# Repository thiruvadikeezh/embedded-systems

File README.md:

🚀 Embedded Systems Adventure Hub
Welcome to my Embedded Systems repository—a vibrant showcase of my thrilling journey into the heart of hardware and software! 🌟 Here, I explore the art & science of embedded systems, crafting innovative projects and sharing my passion for microcontrollers, sensors, and real-time tech.

🌟 About My Journey
I'm on a mission to conquer the world of embedded systems! From blinking LEDs on an Arduino to building IoT marvels with Raspberry Pi and STM32, this repo is my playground for mastering low-level programming and hardware wizardry. Expect a mix of creativity, problem-solving, and a dash of geeky fun as I dive into the nitty-gritty of embedded tech! 💻🔧

🛠 What's Inside

🔥 Exciting Projects: From smart IoT gadgets to sensor-driven systems and real-time applications, explore my hands-on creations.
💾 Code Goodies: Clean, reusable C/C++ snippets for microcontrollers, including drivers, firmware, and more.
📚 Tutorials & Insights: My personal cheat sheets on interrupts, timers, and protocols like I2C, SPI, and UART—perfect for beginners and pros alike.
🔗 Resource Treasure Trove: Curated links to tools, datasheets, and must-have references for embedded enthusiasts.

🚀 Get Started

Clone the Repo: git clone https://github.com/fatmanweb3/embedded-systems.git
Dive into Projects: Browse folders for specific platforms (Arduino, STM32, ESP32) or project types.
Set Up Your Toolkit: Grab Arduino IDE, PlatformIO, or STM32CubeIDE to jump in.
Join the Fun: Got ideas? Open an issue, suggest features, or collaborate on something epic!

🌈 What's Next?
I'm always tinkering and learning! Expect new projects, deep dives into real-time operating systems (RTOS), low-power optimizations, and advanced protocols. Follow along as I push the boundaries of what's possible in embedded systems! 🚀

🤝 Connect & Contribute
Love embedded systems? Let's geek out together! Open a pull request, share your thoughts, or just say hi. Together, we can build mind-blowing tech that powers the future. 💡
Happy hacking, and let's make some hardware magic! ✨

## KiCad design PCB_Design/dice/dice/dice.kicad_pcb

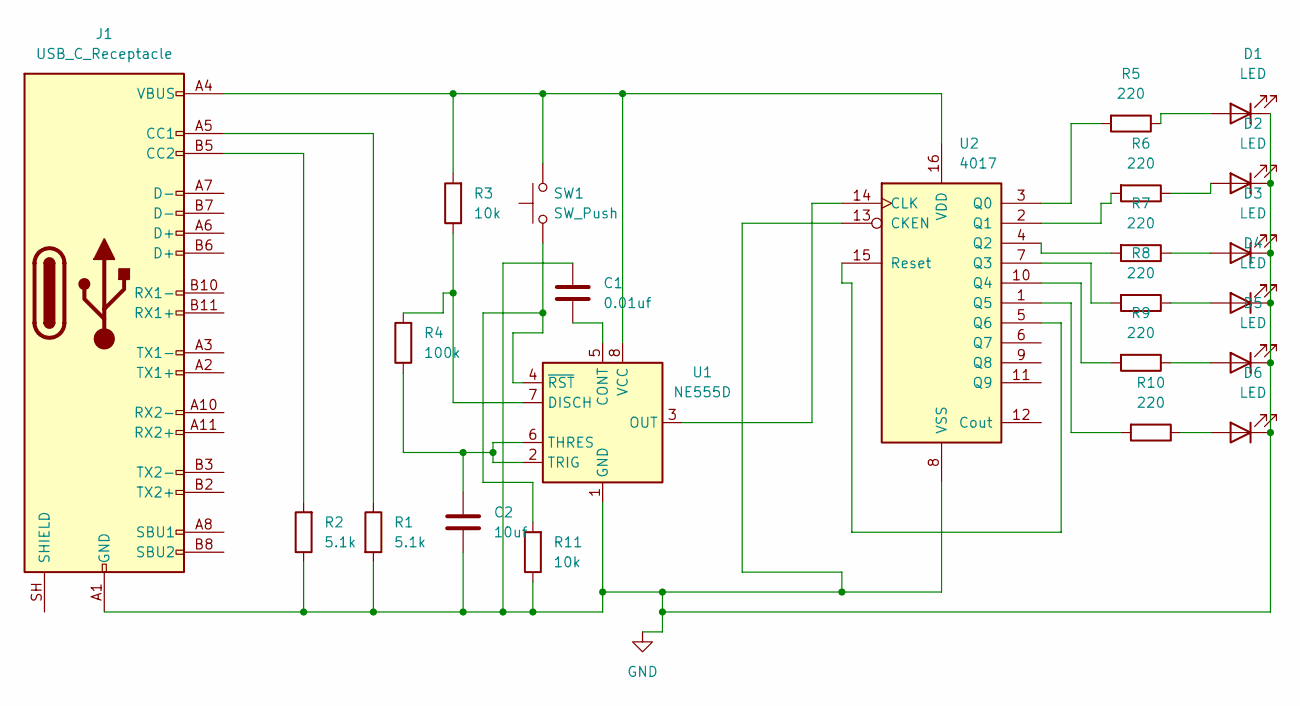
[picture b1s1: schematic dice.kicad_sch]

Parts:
C1: 0.01uf; C_0805_2012Metric
C2: 10uf; C_0805_2012Metric
D1, D2, D3, D4, D5, D6: LED; LED_0805_2012Metric
J1: USB_C_Receptacle; USB_C_Receptacle_HRO_TYPE-C-31-M-12
R1, R2: 5.1k; R_0805_2012Metric
R3, R11: 10k; R_0805_2012Metric
R4: 100k; R_0805_2012Metric
R5, R6, R7, R8, R9, R10: 220; R_0805_2012Metric
SW1: SW_Push; SW_Push_1P1T-MP_NO_Horizontal_Alps_SKRTLAE010
U1: NE555D; SOIC-8_3.9x4.9mm_P1.27mm
U2: 4017; SOIC-16_3.9x9.9mm_P1.27mm

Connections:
GND: C1.1, C2.2, D1.1 (K), D2.1 (K), D3.1 (K), D4.1 (K), D5.1 (K), D6.1 (K), J1.A1 (GND), J1.A12 (GND), J1.B1 (GND), J1.B12 (GND), R1.2, R2.1, R11.1, U1.1 (GND), U2.8 (VSS), U2.13 (CKEN)
unnamed: D1.2 (A), R5.1
unnamed: D2.2 (A), R6.1
unnamed: D3.2 (A), R7.1
unnamed: D4.2 (A), R8.1
unnamed: D5.2 (A), R9.1
unnamed: D6.2 (A), R10.1
unnamed: J1.A5 (CC1), R1.1
unnamed: J1.B5 (CC2), R2.2
unnamed: C1.2, U1.5 (CONT)
unnamed: R3.1, R4.2, U1.7 (DISCH)
unnamed: U1.3 (OUT), U2.14 (CLK)
unnamed: C2.1, R4.1, U1.2 (TRIG), U1.6 (THRES)
unnamed: J1.A4 (VBUS), J1.A9 (VBUS), J1.B4 (VBUS), J1.B9 (VBUS), R3.2, SW1.2, U1.8 (VCC), U2.16 (VDD)
unnamed: R11.2, SW1.1, U1.4 (~RST)
unnamed: R5.2, U2.3 (Q0)
unnamed: R6.2, U2.2 (Q1)
unnamed: R7.2, U2.4 (Q2)
unnamed: R8.2, U2.7 (Q3)
unnamed: R9.2, U2.10 (Q4)
unnamed: R10.2, U2.1 (Q5)
unnamed: U2.5 (Q6), U2.15 (Reset)

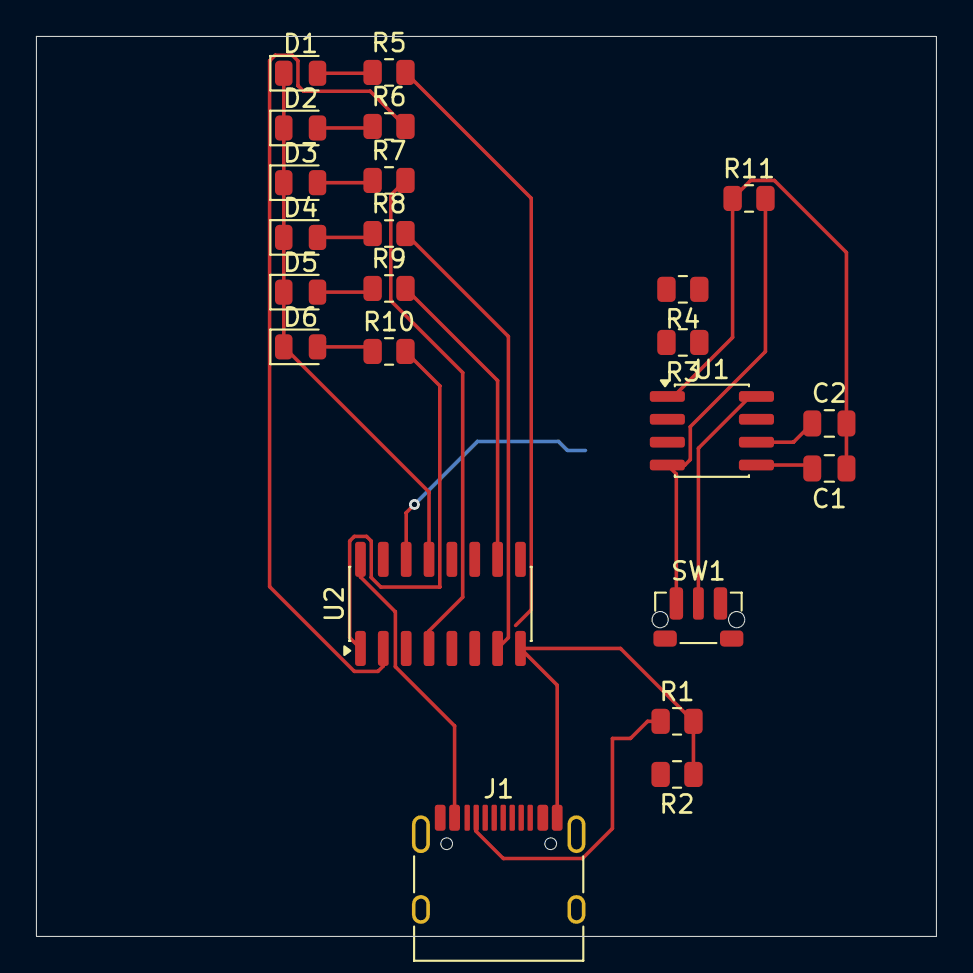
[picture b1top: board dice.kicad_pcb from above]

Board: 2 copper layers, 50.0 x 50.0 mm, 23 parts (0 on the bottom side), 22 nets.

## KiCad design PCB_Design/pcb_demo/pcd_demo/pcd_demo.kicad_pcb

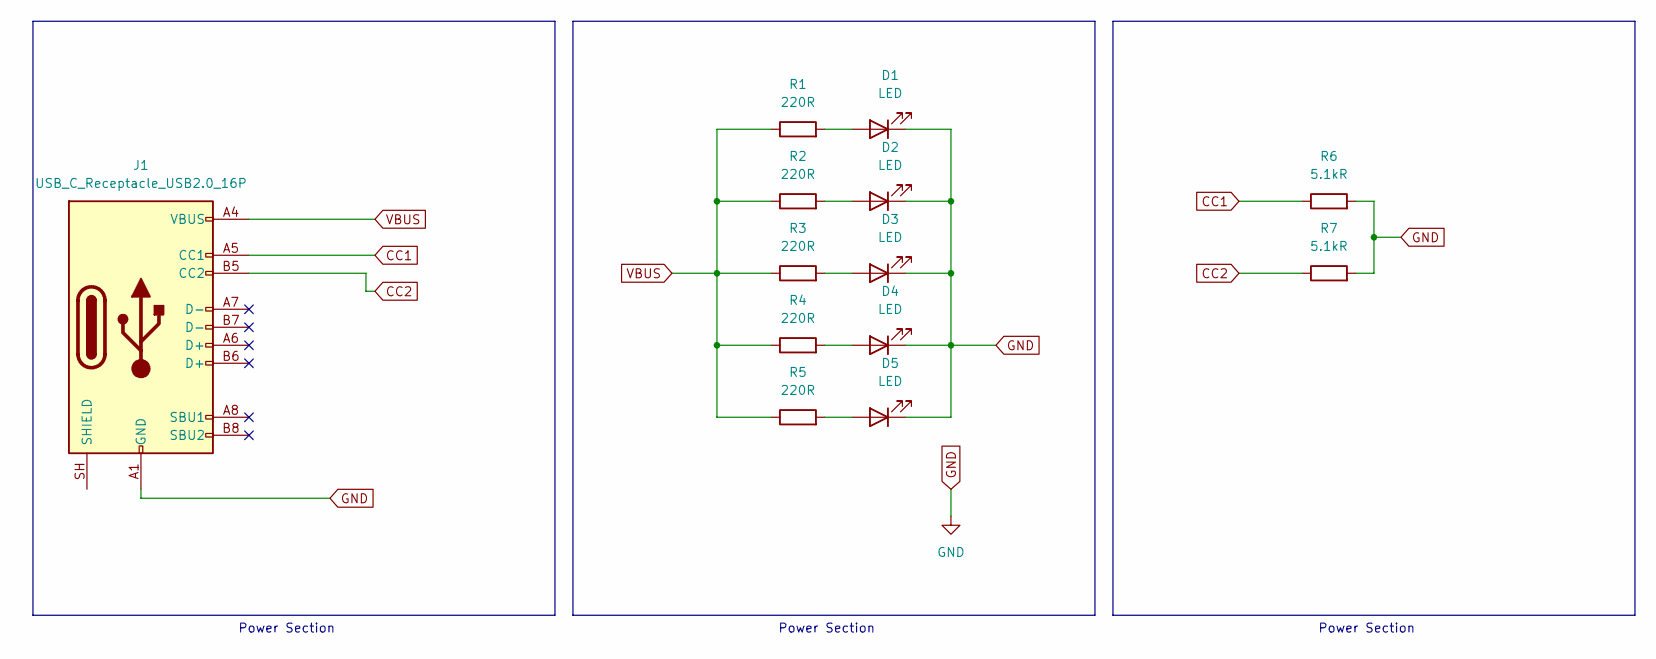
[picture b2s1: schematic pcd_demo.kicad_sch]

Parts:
D1, D2, D3, D4, D5: LED; LED_0805_2012Metric
J1: USB_C_Receptacle_USB2.0_16P
R1, R2, R3, R4, R5: 220R; R_0805_2012Metric
R6, R7: 5.1kR; R_0805_2012Metric

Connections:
CC1: J1.A5 (CC1), R6.1; also elsewhere on the board
CC2: J1.B5 (CC2), R7.1; also elsewhere on the board
GND: D1.1 (K), D2.1 (K), D3.1 (K), D4.1 (K), D5.1 (K), J1.A1 (GND), J1.A12 (GND), J1.B1 (GND), J1.B12 (GND), R6.2, R7.2; also elsewhere on the board
unnamed: D1.2 (A), R1.2
unnamed: D2.2 (A), R2.2
unnamed: D3.2 (A), R3.2
unnamed: D4.2 (A), R4.2
unnamed: D5.2 (A), R5.2
VBUS: J1.A4 (VBUS), J1.A9 (VBUS), J1.B4 (VBUS), J1.B9 (VBUS), R1.1, R2.1, R3.1, R4.1, R5.1; also elsewhere on the board

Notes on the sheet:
Power Section

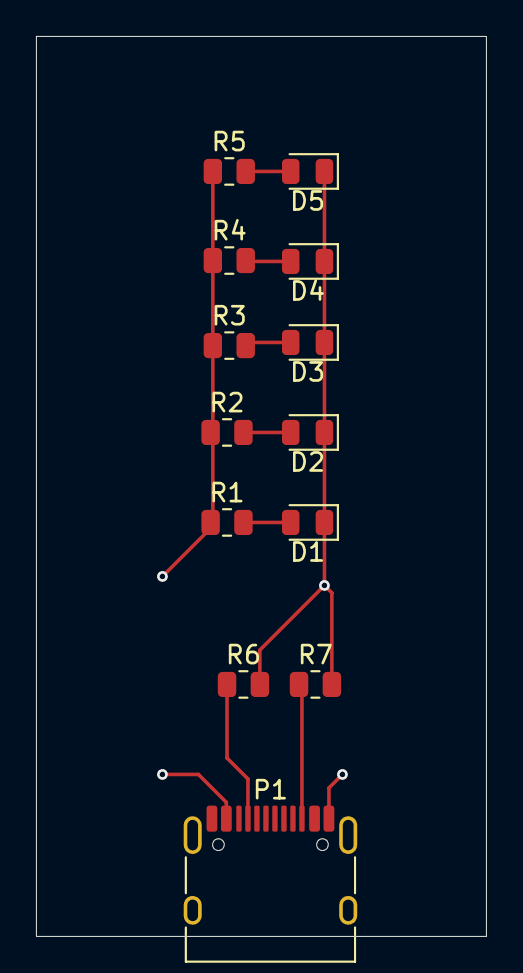
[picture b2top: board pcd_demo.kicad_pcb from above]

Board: 4 copper layers, 25.0 x 50.0 mm, 13 parts (0 on the bottom side), 9 nets.

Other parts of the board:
P1: USB_C_Plug; USB_C_Receptacle_HRO_TYPE-C-31-M-12

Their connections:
CC1: P1.A5 (CC); also elsewhere on the board
CC2: P1.B5 (VCONN); also elsewhere on the board
GND: P1.A1 (GND), P1.A12 (GND), P1.B1 (GND), P1.B12 (GND); also elsewhere on the board
VBUS: P1.A4 (VBUS), P1.A9 (VBUS), P1.B4 (VBUS), P1.B9 (VBUS); also elsewhere on the board

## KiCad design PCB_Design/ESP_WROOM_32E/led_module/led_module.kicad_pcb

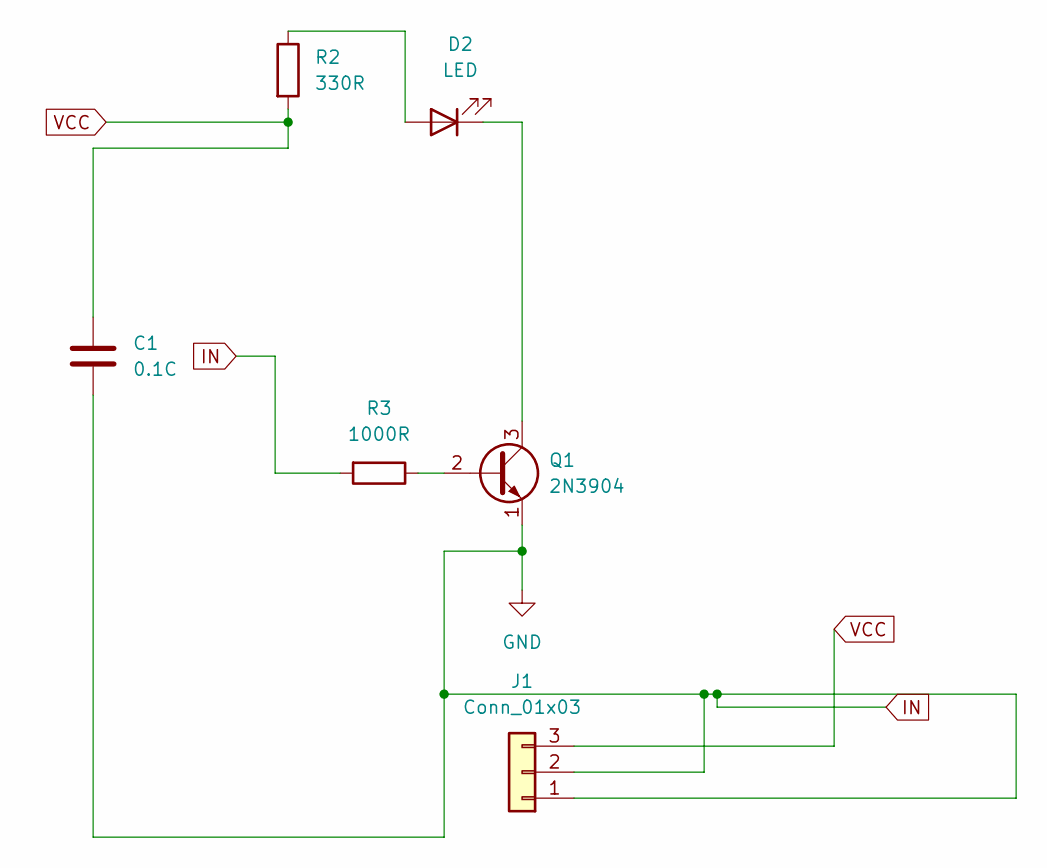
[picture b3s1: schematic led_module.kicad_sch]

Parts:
C1: 0.1C; C_Disc_D5.0mm_W2.5mm_P5.00mm
D2: LED; LED_D5.0mm
J1: Conn_01x03; PinHeader_1x03_P2.54mm_Vertical
Q1: 2N3904; TO-92L_Inline
R2: 330R; R_Axial_DIN0207_L6.3mm_D2.5mm_P7.62mm_Horizontal
R3: 1000R; R_Axial_DIN0207_L6.3mm_D2.5mm_P7.62mm_Horizontal

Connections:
IN: C1.2, J1.1, J1.2, Q1.1 (E), R3.2
unnamed: D2.2 (A), R2.1
unnamed: D2.1 (K), Q1.3 (C)
unnamed: Q1.2 (B), R3.1
VCC: C1.1, J1.3, R2.2

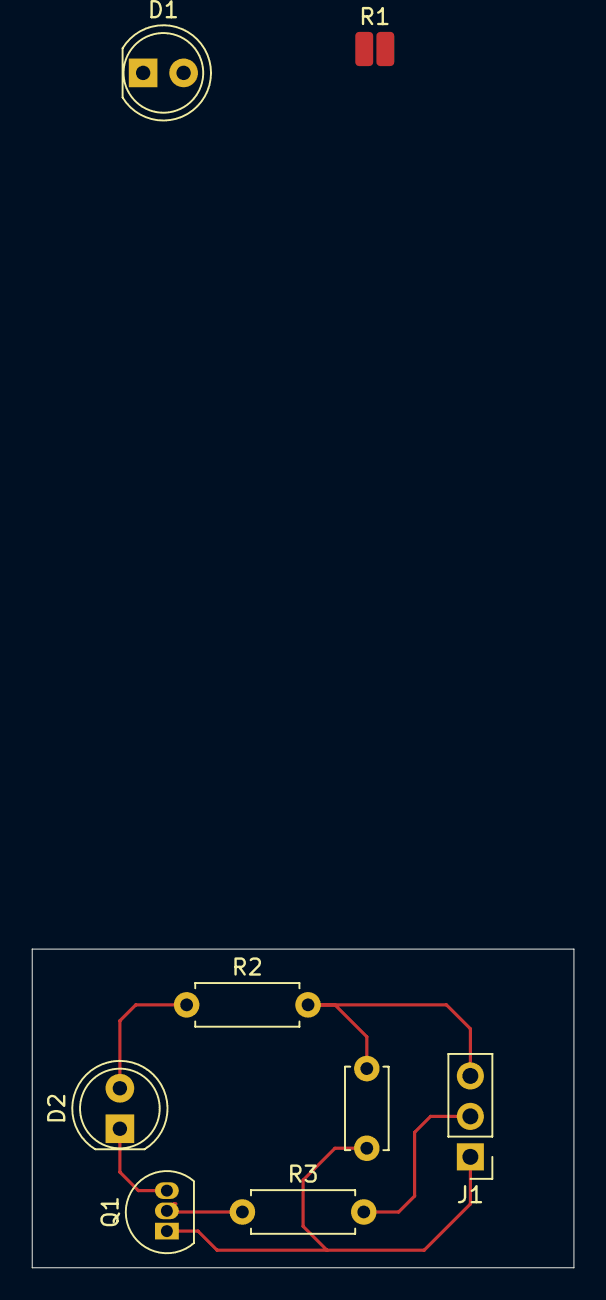
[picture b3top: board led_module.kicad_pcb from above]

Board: 2 copper layers, 34.0 x 20.0 mm, 8 parts (0 on the bottom side), 5 nets.

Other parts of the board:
D1: LED; LED_D5.0mm
R1: R; R_0508_1220Metric_Pad1.12x2.15mm_HandSolder

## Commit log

2025-10-23 added pico support
2025-10-26 adding support for pico_2w
2025-11-13 trying toolchains etup
2025-11-16 adding pcb designs for led module
2026-01-12 genral backup
2026-01-12 general backup
2026-01-26 ef32bg22 dev board
2026-01-26 chore: clean up build files and add si labs dev board
2026-04-19 electronic dice project
2026-04-20 added footprints and started routing with board dimensions
2026-05-01 backup pcb
2026-05-10 usb led pcb
